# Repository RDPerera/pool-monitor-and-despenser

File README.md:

# Pool Monitor and Chemical Dispenser System

A comprehensive IoT solution for pool management featuring:
- **ESP32-based Chemical Dispenser** with WiFi Manager and remote control
- **Flask REST API** for pool monitoring and chemical management
- **Flutter Mobile App** for monitoring and control (in development)
- **Cloudflare Tunnel** integration for secure remote access

## 🚀 Quick Start

### Chemical Dispenser System (NEW!)

**Hardware:** ESP32 + 4-channel relay module + pumps

**Quick Setup:**
```bash
# 1. Start the server
cd server
./start_server.sh

# 2. Start Cloudflare tunnel (for testing)
cloudflared tunnel --url http://localhost:5000

# 3. Update ESP32 firmware with tunnel URL and upload
# 4. Configure WiFi on ESP32 (long press button > 5 sec)
# 5. Test dispensing!
```

**Complete Documentation:**
- 📘 [**DISPENSER_README.md**](DISPENSER_README.md) - Main dispenser guide
- 📗 [**DISPENSER_SETUP.md**](DISPENSER_SETUP.md) - Detailed setup instructions
- 📙 [**CLOUDFLARE_TUNNEL_SETUP.md**](CLOUDFLARE_TUNNEL_SETUP.md) - Tunnel configuration
- 📝 [**QUICK_REFERENCE.md**](QUICK_REFERENCE.md) - Quick reference card
- 🔌 [**WIRING_DIAGRAM.txt**](WIRING_DIAGRAM.txt) - Hardware wiring diagrams

### Pool Monitor API

A Flask-based REST API for monitoring pool water quality and managing chemical dispenser data.

## Features

### Chemical Dispenser System
- ✅ **WiFi Manager** - Easy WiFi configuration via captive portal
- ✅ **4 Independent Dispensers** - Control 4 chemical pumps separately
- ✅ **Remote Control** - Access from anywhere via Cloudflare Tunnel
- ✅ **LED Status Indicators** - Visual feedback for all states
- ✅ **Test Mode** - Quick button press to test all pumps
- ✅ **Auto-Reset** - Automatically clears jobs after dispensing
- ✅ **JSON Configuration** - Easy-to-modify settings

### Pool Monitoring API
- Pool water quality monitoring (pH, turbidity, temperature)
- Device management and configuration
- Chemical dispenser data management
- Real-time alerts for critical conditions
- SQLite database with SQLAlchemy ORM

## Installation

### Server Setup

1. Navigate to the server directory:
```bash
cd server
```

2. **Quick Start** (recommended):
```bash
./start_server.sh
```

**OR Manual Setup:**

3. Create and activate virtual environment:
```bash
python3 -m venv venv
source venv/bin/activate  # On Windows: venv\Scripts\activate
```

4. Install dependencies:
```bash
pip install -r requirements.txt
```

5. Run the application:
```bash
python main.py
```

The server will start on http://localhost:5000

### ESP32 Firmware Setup

See [DISPENSER_SETUP.md](DISPENSER_SETUP.md) for complete instructions.

**Quick version:**
1. Install Arduino IDE + ESP32 support + required libraries
2. Open `dispenser/firmware.ino`
3. Update API URLs with your Cloudflare tunnel URL
4. Upload to ESP32
5. Configure WiFi (long press button > 5 seconds)

## API Endpoints

### Chemical Dispenser Endpoints (NEW!)

#### Get Dispenser Values
```http
GET /api/dispenser/get
```
Returns current dispenser time values (in seconds).

**Response:**
```json
{
  "dispenser1": "0",
  "dispenser2": "0",
  "dispenser3": "0",
  "dispenser4": "0"
}
```

#### Set Dispenser Values
```http
POST /api/dispenser/set
Content-Type: application/json

{
  "dispenser1": "5",
  "dispenser2": "3",
  "dispenser3": "2",
  "dispenser4": "4"
}
```

**Response:**
```json
{
  "message": "Dispenser values updated successfully",
  "config": {
    "dispenser1": "5",
    "dispenser2": "3",
    "dispenser3": "2",
    "dispenser4": "4"
  }
}
```

#### Reset Dispenser Values
```http
POST /api/dispenser/reset
```
Resets all dispenser values to "0".

**Response:**
```json
{
  "message": "Dispenser values reset successfully",
  "config": {
    "dispenser1": "0",
    "dispenser2": "0",
    "dispenser3": "0",
    "dispenser4": "0"
  }
}
```

### Authentication Endpoints

#### User Registration and Login
- `POST /api/auth/register` - Register a new user
- `POST /api/auth/login` - Login and get JWT token
- `GET /api/auth/profile` - Get current user profile (requires auth)
- `PUT /api/auth/profile` - Update user profile (requires auth)
- `PUT /api/auth/change-password` - Change user password (requires auth)
- `GET /api/users` - Get all users (admin only, requires auth)

### Pool Monitor Endpoints

#### Device Data Collection
- `POST /pool/data` - Receive sensor data from ESP32 devices
- `GET /pool/config?device_id=<id>` - Get device configuration

#### Device Management
- `GET /api/devices` - Get all registered devices
- `GET /api/devices/<device_id>` - Get specific device information  
- `PUT /api/devices/<device_id>` - Update device information

#### Device Readings
- `GET /api/devices/<device_id>/readings` - Get sensor readings (limited to 100 records)
  - Query parameters: `limit` (max 100), `hours` (filter by time)
- `GET /api/devices/<device_id>/latest` - Get latest sensor reading

#### Device Configuration
- `GET /api/devices/<device_id>/config` - Get device configuration
- `POST /api/devices/<device_id>/config` - Create device configuration
- `PUT /api/devices/<device_id>/config` - Update device configuration

#### Statistics
- `GET /api/stats/<device_id>` - Get device statistics
  - Query parameters: `hours` (default: 24)

### Chemical Dispensing Jobs Endpoints

#### CRUD Operations for Chemical Dispensing Jobs
- `POST /api/dispensing-jobs` - Create new chemical dispensing job
- `GET /api/dispensing-jobs` - Get PENDING dispensing jobs (limited to 100 records)
  - Query parameters: `limit` (max 100), `device_id` (filter by device)
- `GET /api/dispensing-jobs/<device_id>` - Get dispensing jobs for specific device
  - Query parameters: `limit` (max 100), `status` (default: PENDING)
- `GET /api/dispensing-jobs/all` - Get ALL dispensing jobs for tracking (including completed)
  - Query parameters: `limit` (max 500), `device_id` (filter by device), `status` (filter by status)
- `PUT /api/dispensing-jobs/<record_id>` - Update dispensing job record

### Chemical Dispensing Jobs Data Format

The chemical dispensing system manages the following job data:

```json
{
  "id": 1,
  "device_id": "ESP32_CHEM_001",
  "hcl": 10.0,
  "soda": 12.0,
  "cl": 0.0,
  "al": 0.0,
  "flag": "PENDING",
  "timestamp": "2023-01-01T10:00:00"
}
```

**Fields:**
- `device_id`: Chemical dispensing device identifier (string)
- `hcl`: Hydrochloric acid level (float)
- `soda`: Soda ash level (float) 
- `cl`: Chlorine level (float)
- `al`: Aluminum level (float)
- `flag`: Status flag (string, e.g., "PENDING", "COMPLETED", "ERROR")
- `timestamp`: ISO format timestamp

## API Sample Payloads and Examples

### 1. Authentication Endpoints

#### Register a New User
**POST** `/api/auth/register`

**Request Payload:**
```json
{
  "email": "john.doe@example.com",
  "password": "secure_password123",
  "first_name": "John",
  "last_name": "Doe",
  "role": "user"
}
```

**Sample cURL:**
```bash
curl -X POST http://localhost:5000/api/auth/register \
  -H "Content-Type: application/json" \
  -d '{
    "email": "john.doe@example.com",
    "password": "secure_password123",
    "first_name": "John",
    "last_name": "Doe"
  }'
```

**Response:**
```json
{
  "message": "User registered successfully",
  "user": {
    "id": 1,
    "email": "john.doe@example.com",
    "first_name": "John",
    "last_name": "Doe",
    "role": "user",
    "is_active": true,
    "created_at": "2023-12-16T14:30:00.000000",
    "last_login": null
  },
  "token": "eyJ0eXAiOiJKV1QiLCJhbGciOiJIUzI1NiJ9..."
}
```

#### Login User
**POST** `/api/auth/login`

**Request Payload:**
```json
{
  "email": "john.doe@example.com",
  "password": "secure_password123"
}
```

**Sample cURL:**
```bash
curl -X POST http://localhost:5000/api/auth/login \
  -H "Content-Type: application/json" \
  -d '{
    "email": "john.doe@example.com",
    "password": "secure_password123"
  }'
```

#### Update Profile
**PUT** `/api/auth/profile`

**Request Payload:**
```json
{
  "first_name": "John Updated",
  "last_name": "Doe Updated"
}
```

**Sample cURL:**
```bash
curl -X PUT http://localhost:5000/api/auth/profile \
  -H "Content-Type: application/json" \
  -H "Authorization: Bearer YOUR_JWT_TOKEN" \
  -d '{
    "first_name": "John Updated",
    "last_name": "Doe Updated"
  }'
```

#### Change Password
**PUT** `/api/auth/change-password`

**Request Payload:**
```json
{
  "current_password": "secure_password123",
  "new_password": "new_secure_password456"
}
```

### 2. Pool Monitor Device Endpoints

#### Send Device Data (ESP32)
**POST** `/pool/data`

**Request Payload:**
```json
{
  "device_id": "ESP32_POOL_001",
  "sensors": {
    "ph": 7.2,
    "turbidity": 3.5,
    "temperature": 26.8
  },
  "status": {
    "water_quality": "optimal",
    "wifi_rssi": -65,
    "uptime": 3600
  }
}
```

**Sample cURL:**
```bash
curl -X POST http://localhost:5000/pool/data \
  -H "Content-Type: application/json" \
  -d '{
    "device_id": "ESP32_POOL_001",
    "sensors": {
      "ph": 7.2,
      "turbidity": 3.5,
      "temperature": 26.8
    },
    "status": {
      "water_quality": "optimal",
      "wifi_rssi": -65,
      "uptime": 3600
    }
  }'
```

#### Update Device Information
**PUT** `/api/devices/<device_id>`

**Request Payload:**
```json
{
  "name": "Backyard Pool Monitor",
  "location": "Main Pool Area - Southeast Corner"
}
```

**Sample cURL:**
```bash
curl -X PUT http://localhost:5000/api/devices/ESP32_POOL_001 \
  -H "Content-Type: application/json" \
  -d '{
    "name": "Backyard Pool Monitor",
    "location": "Main Pool Area - Southeast Corner"
  }'
```

### 3. Device Configuration Endpoints

#### Create Device Configuration
**POST** `/api/devices/<device_id>/config`

**Request Payload:**
```json
{
  "calibration": {
    "ph_offset": 0.1,
    "ph_slope": 0.98,
    "turbidity_offset": -0.5,
    "turbidity_slope": 1.02,
    "temp_offset": 0.2
  },
  "thresholds": {
    "ph": {
      "optimal": 7.2,
      "acceptable": 7.8,
      "critical": 8.5
    },
    "turbidity": {
      "optimal": 5.0,
      "acceptable": 20.0,
      "critical": 50.0
    },
    "temperature": {
      "optimal": 26.0,
      "acceptable": 30.0,
      "critical": 33.0
    }
  },
  "intervals": {
    "post_interval": 2000,
    "config_interval": 60000
  }
}
```

**Sample cURL:**
```bash
curl -X POST http://localhost:5000/api/devices/ESP32_POOL_001/config \
  -H "Content-Type: application/json" \
  -d '{
    "thresholds": {
      "ph": {"optimal": 7.2, "acceptable": 7.8, "critical": 8.5},
      "turbidity": {"optimal": 5.0, "acceptable": 20.0, "critical": 50.0},
      "temperature": {"optimal": 26.0, "acceptable": 30.0, "critical": 33.0}
    },
    "intervals": {"post_interval": 2000, "config_interval": 60000}
  }'
```

#### Update Device Configuration
**PUT** `/api/devices/<device_id>/config`

**Request Payload:**
```json
{
  "thresholds": {
    "ph": {
      "optimal": 7.4,
      "critical": 8.2
    }
  },
  "intervals": {
    "post_interval": 1500
  }
}
```

### 4. Chemical Dispensing Jobs Endpoints

#### Create Chemical Dispensing Job
**POST** `/api/dispensing-jobs`

**Request Payload:**
```json
{
  "device_id": "ESP32_CHEM_001",
  "hcl": 10.5,
  "soda": 12.3,
  "cl": 2.1,
  "al": 0.8,
  "flag": "PENDING",
  "timestamp": "2023-12-16 14:30:00"
}
```

**Sample cURL:**
```bash
curl -X POST http://localhost:5000/api/dispensing-jobs \
  -H "Content-Type: application/json" \
  -d '{
    "device_id": "ESP32_CHEM_001",
    "hcl": 10.5,
    "soda": 12.3,
    "cl": 2.1,
    "al": 0.8,
    "flag": "PENDING",
    "timestamp": "2023-12-16 14:30:00"
  }'
```

**Response:**
```json
{
  "id": 1,
  "device_id": "ESP32_CHEM_001",
  "hcl": 10.5,
  "soda": 12.3,
  "cl": 2.1,
  "al": 0.8,
  "flag": "PENDING",
  "timestamp": "2023-12-16T14:30:00"
}
```

#### Update Chemical Dispensing Job
**PUT** `/api/dispensing-jobs/<record_id>`

**Request Payload:**
```json
{
  "flag": "IN_PROGRESS",
  "hcl": 11.2,
  "soda": 13.1
}
```

**Sample cURL:**
```bash
curl -X PUT http://localhost:5000/api/dispensing-jobs/1 \
  -H "Content-Type: application/json" \
  -d '{
    "flag": "IN_PROGRESS",
    "hcl": 11.2,
    "soda": 13.1
  }'
```

### 5. Sample GET Responses

#### Get All Devices
**GET** `/api/devices`

**Response:**
```json
[
  {
    "id": 1,
    "device_id": "ESP32_POOL_001",
    "name": "Backyard Pool Monitor",
    "location": "Main Pool Area - Southeast Corner",
    "registered_at": "2023-12-16T10:00:00.000000",
    "last_seen": "2023-12-16T14:30:00.000000"
  }
]
```

#### Get Device Readings
**GET** `/api/devices/ESP32_POOL_001/readings?limit=5`

**Response:**
```json
[
  {
    "id": 150,
    "device_id": "ESP32_POOL_001",
    "timestamp": "2023-12-16T14:30:00.000000",
    "ph": 7.2,
    "turbidity": 3.5,
    "temperature": 26.8,
    "water_quality": "optimal",
    "wifi_rssi": -65,
    "uptime": 3600
  },
  {
    "id": 149,
    "device_id": "ESP32_POOL_001",
    "timestamp": "2023-12-16T14:29:00.000000",
    "ph": 7.1,
    "turbidity": 3.8,
    "temperature": 26.9,
    "water_quality": "optimal",
    "wifi_rssi": -67,
    "uptime": 3540
  }
]
```

#### Get Chemical Dispensing Jobs (PENDING Jobs Only)
**GET** `/api/dispensing-jobs?limit=3`

**Response:**
```json
[
  {
    "id": 5,
    "device_id": "ESP32_CHEM_001",
    "hcl": 11.2,
    "soda": 13.1,
    "cl": 2.1,
    "al": 0.8,
    "flag": "PENDING",
    "timestamp": "2023-12-16T14:35:00"
  },
  {
    "id": 4,
    "device_id": "ESP32_CHEM_002",
    "hcl": 10.8,
    "soda": 12.5,
    "cl": 1.9,
    "al": 0.7,
    "flag": "PENDING",
    "timestamp": "2023-12-16T14:20:00"
  },
  {
    "id": 3,
    "device_id": "ESP32_CHEM_001",
    "hcl": 10.5,
    "soda": 12.3,
    "cl": 2.1,
    "al": 0.8,
    "flag": "PENDING",
    "timestamp": "2023-12-16T14:10:00"
  }
]
```

#### Get Device Statistics
**GET** `/api/stats/ESP32_POOL_001?hours=24`

**Response:**
```json
{
  "period_hours": 24,
  "total_readings": 1440,
  "ph": {
    "avg": 7.25,
    "min": 6.9,
    "max": 7.6
  },
  "turbidity": {
    "avg": 4.2,
    "min": 2.1,
    "max": 8.9
  },
  "temperature": {
    "avg": 26.8,
    "min": 24.2,
    "max": 29.1
  }
}
```

### 6. Query Parameters Examples

```bash
# Get device readings with custom limit and time filter
curl "http://localhost:5000/api/devices/ESP32_POOL_001/readings?limit=50&hours=12"

# Get dispensing jobs data with limit
curl "http://localhost:5000/api/dispensing-jobs?limit=25"

# Get PENDING jobs for specific device
curl "http://localhost:5000/api/dispensing-jobs?device_id=ESP32_CHEM_001"

# Get jobs by device ID (dedicated endpoint)
curl "http://localhost:5000/api/dispensing-jobs/ESP32_CHEM_001"

# Get jobs by device ID with custom status
curl "http://localhost:5000/api/dispensing-jobs/ESP32_CHEM_001?status=COMPLETED&limit=10"

# Get ALL jobs for tracking (including completed ones)
curl "http://localhost:5000/api/dispensing-jobs/all"

# Get all jobs for specific device (all statuses)
curl "http://localhost:5000/api/dispensing-jobs/all?device_id=ESP32_CHEM_001"

# Get all completed jobs for tracking
curl "http://localhost:5000/api/dispensing-jobs/all?status=COMPLETED&limit=200"

# Get device statistics for last week
curl "http://localhost:5000/api/stats/ESP32_POOL_001?hours=168"

# Get device configuration from ESP32
curl "http://localhost:5000/pool/config?device_id=ESP32_POOL_001"
```

### 7. Error Response Examples

**400 Bad Request:**
```json
{
  "error": "Missing required field: device_id"
}
```

**401 Unauthorized:**
```json
{
  "error": "Token is missing"
}
```

**404 Not Found:**
```json
{
  "error": "Device not found"
}
```

**409 Conflict:**
```json
{
  "error": "Email already exists"
}
```

## Environment Variables

Create a `.env` file in the server directory:

```
DEBUG=True
PORT=500
DATABASE_URL=sqlite:///pool_monitor.db
JWT_SECRET_KEY=your-super-secret-jwt-key-change-in-production
```

## Database Models

The API uses SQLAlchemy with the following models:
- `Device` (pool_devices) - Pool monitoring devices
- `SensorReading` (pool_sensor_readings) - Sensor data from devices
- `DeviceConfig` (pool_device_configs) - Device configuration and calibration
- `Alert` (pool_alerts) - Critical condition alerts
- `ChemicalDispenser` (chemical_dispenser_jobs) - Chemical dispenser job data
- `User` (user_accounts) - User authentication data

## Project Structure

```
pool-monitor-and-dispenser/
├── README.md
├── firmware/
│   └── firmware.ino
└── server/
    ├── main.py
    ├── dependencies.txt
    └── instance/
```

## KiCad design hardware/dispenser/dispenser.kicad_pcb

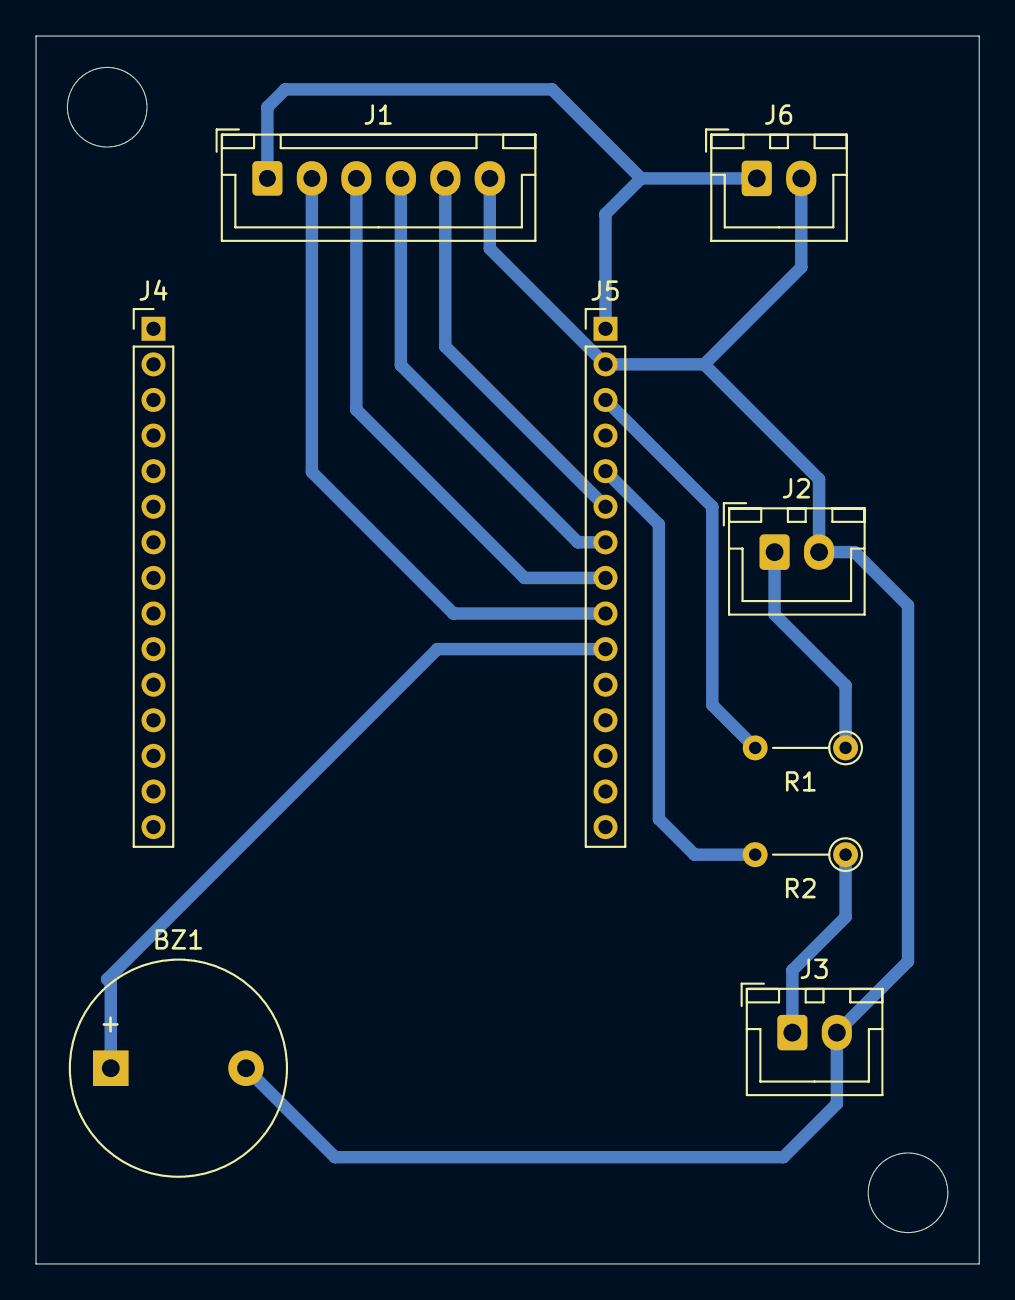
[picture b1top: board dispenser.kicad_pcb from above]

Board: 2 copper layers, 53.0 x 69.0 mm, 9 parts (0 on the bottom side), 11 nets.

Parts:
BZ1: Buzzer; Buzzer_12x9.5RM7.6
J1: Conn_01x06_Pin; JST_XH_B6B-XH-A_1x06_P2.50mm_Vertical
J2, J3, J6: Conn_01x02_Pin; JST_XH_B2B-XH-A_1x02_P2.50mm_Vertical
J4, J5: Conn_01x15_Socket; PinHeader_1x15_P2.00mm_Vertical
R1, R2: 220R; R_Axial_DIN0204_L3.6mm_D1.6mm_P5.08mm_Vertical

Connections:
+5V: J1.1, J5.1, J6.1
GND: BZ1.2 (-), J1.6, J2.2, J3.2, J5.2, J6.2
unnamed: BZ1.1 (+), J5.10
unnamed: J1.2, J5.9
unnamed: J1.3, J5.8
unnamed: J1.4, J5.7
unnamed: J1.5, J5.6
unnamed: J2.1, R1.1
unnamed: J3.1, R2.1
unnamed: J5.3, R1.2
unnamed: J5.5, R2.2

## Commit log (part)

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2025-11-13 Implement Pool Water Quality Monitor firmware and server API
    - Added firmware code for ESP32 to monitor pool water quality (pH, turbidity, temperature).
    - Integrated WiFiManager for easy WiFi configuration.
    - Implemented sensor reading, data posting to API, and configuration fetching.
    - Created server-side API using Flask to handle incoming data and serve device configurations.
    - Established database models for devices, sensor readings, configurations, and alerts.
    - Added environment configuration using .env file for database and server settings.
2025-11-14 Add initial database file and update temperature threshold comment in DeviceConfig model
2025-12-16 Added updated server code
2025-12-16 Refactor chemical dispenser API endpoints and database models for clarity and consistency
2025-12-18 Add init flutter code
2025-12-18 Add mock data insertion for user, device, and sensor reading in database
2025-12-18 Refactor device data handling and improve error management in DeviceProvider; update API base URL to correct port
2025-12-18 Refactor SensorReading and DispensingJob models to use nullable fields and provide default values for optional parameters
2025-12-18 Enhance SensorReading deserialization to support nested sensor data and improve error handling in getLatestReading method
2025-12-18 Disable debug banner in PoolMonitorApp and remove debug print statement in getLatestReading method
2025-12-24 Refactor dispensing functionality and enhance settings screen
    - Removed the old DispensingScreen and added a new TreatmentsScreen with a user-friendly interface for dispensing control.
    - Updated the SettingsScreen to improve UI with better styling and added icons to input fields for clarity.
    - Added sensors_plus dependency for gyroscope functionality.
    - Updated pubspec.lock and pubspec.yaml to reflect new dependencies.
    - Updated the pool_monitor database instance.
2026-01-22 Add wiring diagram, firmware, and server components for pool chemical dispenser
    - Created wiring diagram for the ESP32 pool chemical dispenser system.
    - Added firmware for ESP32 to handle WiFi connection, API calls, and relay control.
    - Introduced dispenser configuration JSON file for managing dispenser states.
    - Implemented Flask server with API endpoints for getting, setting, and resetting dispenser values.
    - Added requirements.txt for server dependencies and a startup script for server initialization.
    - Included test script for API to validate functionality and simulate ESP32 polling behavior.
2026-01-24 feat: Add WiFi settings screen and app logo widget
    - Created a new WiFiSettingsScreen for managing WiFi settings.
    - Introduced AppLogo widget for consistent branding across the app.
    - Added app logo image asset.
    - Updated pubspec.yaml to include new assets and removed unused dependencies.
    - Modified widget tests to verify the initial route displays the login screen.
    - Enhanced CMakeLists.txt for better compatibility with older Flutter versions.
2026-04-19 Add new flutter app
